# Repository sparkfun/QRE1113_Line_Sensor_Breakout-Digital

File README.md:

SparkFun Line Sensor Breakout - QRE1113 (Digital)
========================================

[*SparkFun Line Sensor Breakout - QRE1113 (Digital) (ROB-09454)*](https://www.sparkfun.com/products/9454)

This version of the QRE1113 breakout board features a digital output, using a capacitor discharge circuit to measure the amount of reflection. 
This tiny board is perfect for line sensing when only digital I/O is available, and can be used in both 3.3V and 5V systems.

Repository Contents
-------------------

* **/Hardware** - Eagle design files (.brd, .sch)
* **/Production** - Production panel files (.brd)

Documentation
--------------
* **[SparkFun Fritzing repo](https://github.com/sparkfun/Fritzing_Parts)** - Fritzing diagrams for SparkFun products.
* **[SparkFun 3D Model repo](https://github.com/sparkfun/3D_Models)** - 3D models of SparkFun products. 

Product Versions
----------------
* [ROB-09454](https://www.sparkfun.com/products/9454)- Digital version of the breakout board. 
* [ROB-09453] (https://www.sparkfun.com/products/9453)- Analog version of the breakout board. 

License Information
-------------------
This product is _**open source**_! 

The **hardware** is released under [Creative Commons ShareAlike 4.0 International](https://creativecommons.org/licenses/by-sa/4.0/).

Please use, reuse, and modify these files as you see fit. Please maintain attribution to SparkFun Electronics and release anything derivative under the same license.

Distributed as-is; no warranty is given.

- Your friends at SparkFun.

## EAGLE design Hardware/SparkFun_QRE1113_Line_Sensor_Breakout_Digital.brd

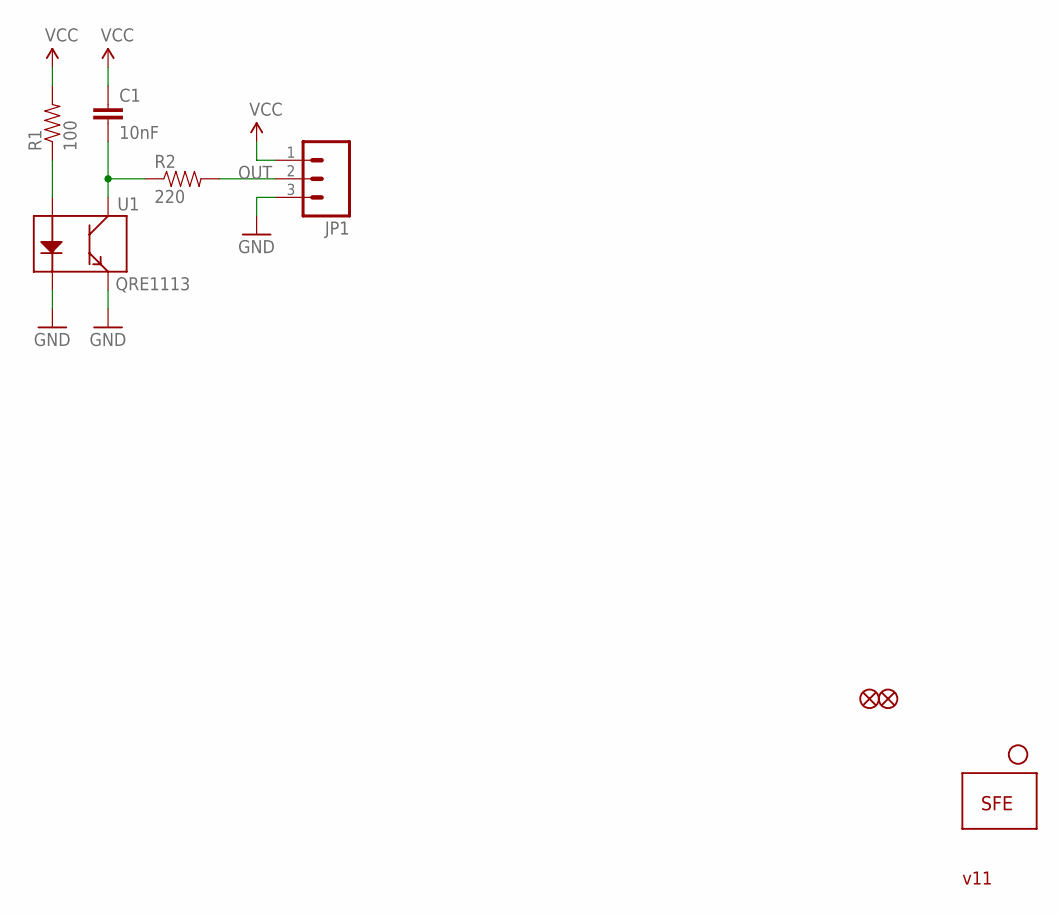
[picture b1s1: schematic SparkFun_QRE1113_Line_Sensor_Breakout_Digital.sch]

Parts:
C1: 10nF; 0402-CAP
FID1, FID2: FIDUCIALUFIDUCIAL; MICRO-FIDUCIAL
JP1: M03PTH; 1X03
JP2: LOGO-SFESK; SFE-LOGO-FLAME
JP3: STAND-OFF
R1: 100; 0402-RES
R2: 220; 0402-RES
U1: QRE1113

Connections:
GND: JP1.3, U1.2 (K), U1.4 (E)
unnamed: R1.1, U1.1 (A)
OUT: JP1.2, R2.2
OUT1: C1.2, R2.1, U1.3 (C)
VCC: C1.1, JP1.1, R1.2

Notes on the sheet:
v11

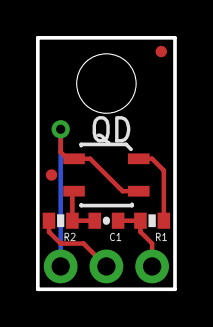
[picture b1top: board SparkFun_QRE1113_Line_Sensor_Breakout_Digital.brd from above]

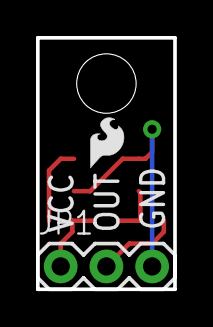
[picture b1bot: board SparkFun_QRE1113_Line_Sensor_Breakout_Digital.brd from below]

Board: 2 copper layers, 7.6 x 14.0 mm, 9 parts (2 on the bottom side), 5 nets.

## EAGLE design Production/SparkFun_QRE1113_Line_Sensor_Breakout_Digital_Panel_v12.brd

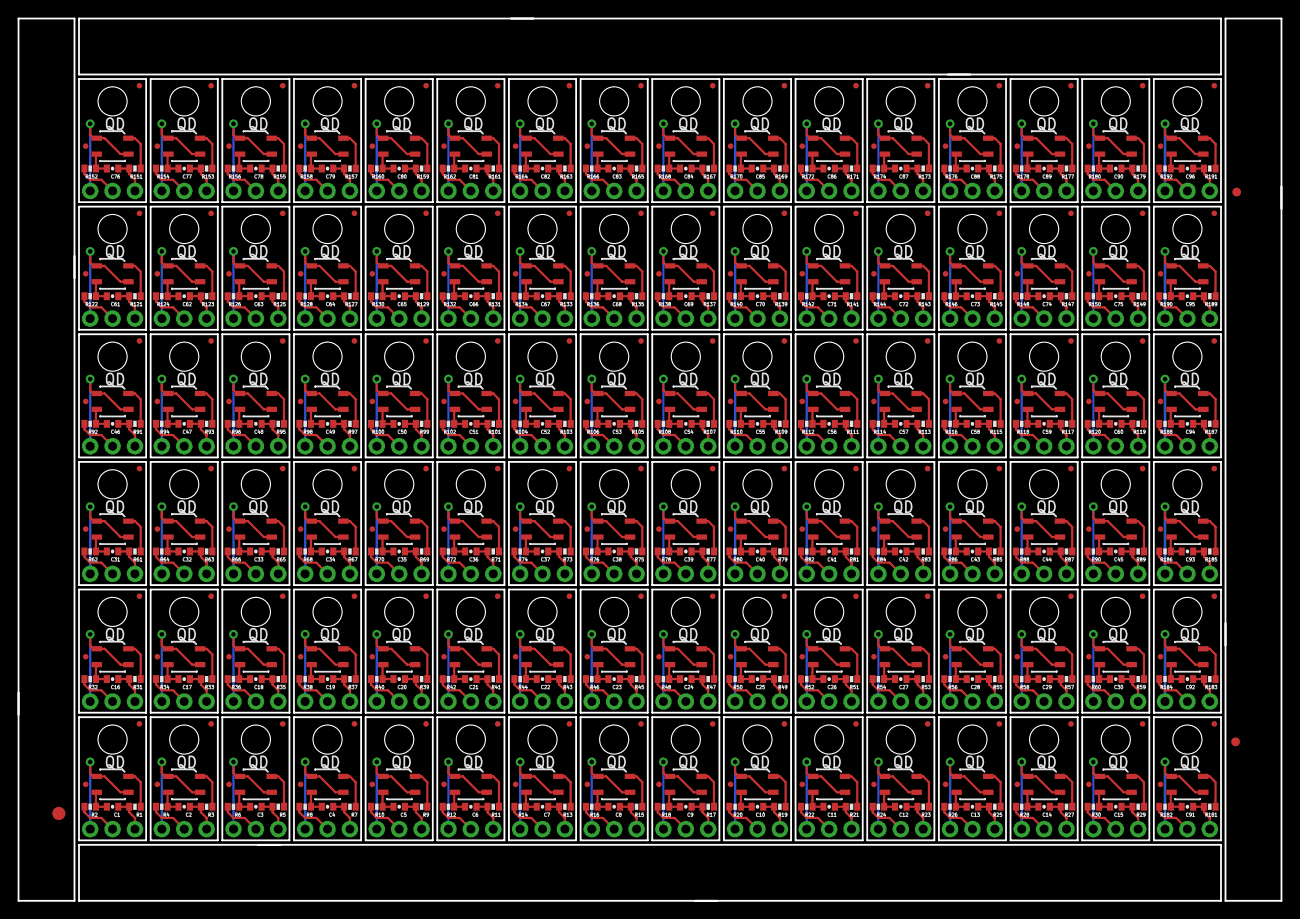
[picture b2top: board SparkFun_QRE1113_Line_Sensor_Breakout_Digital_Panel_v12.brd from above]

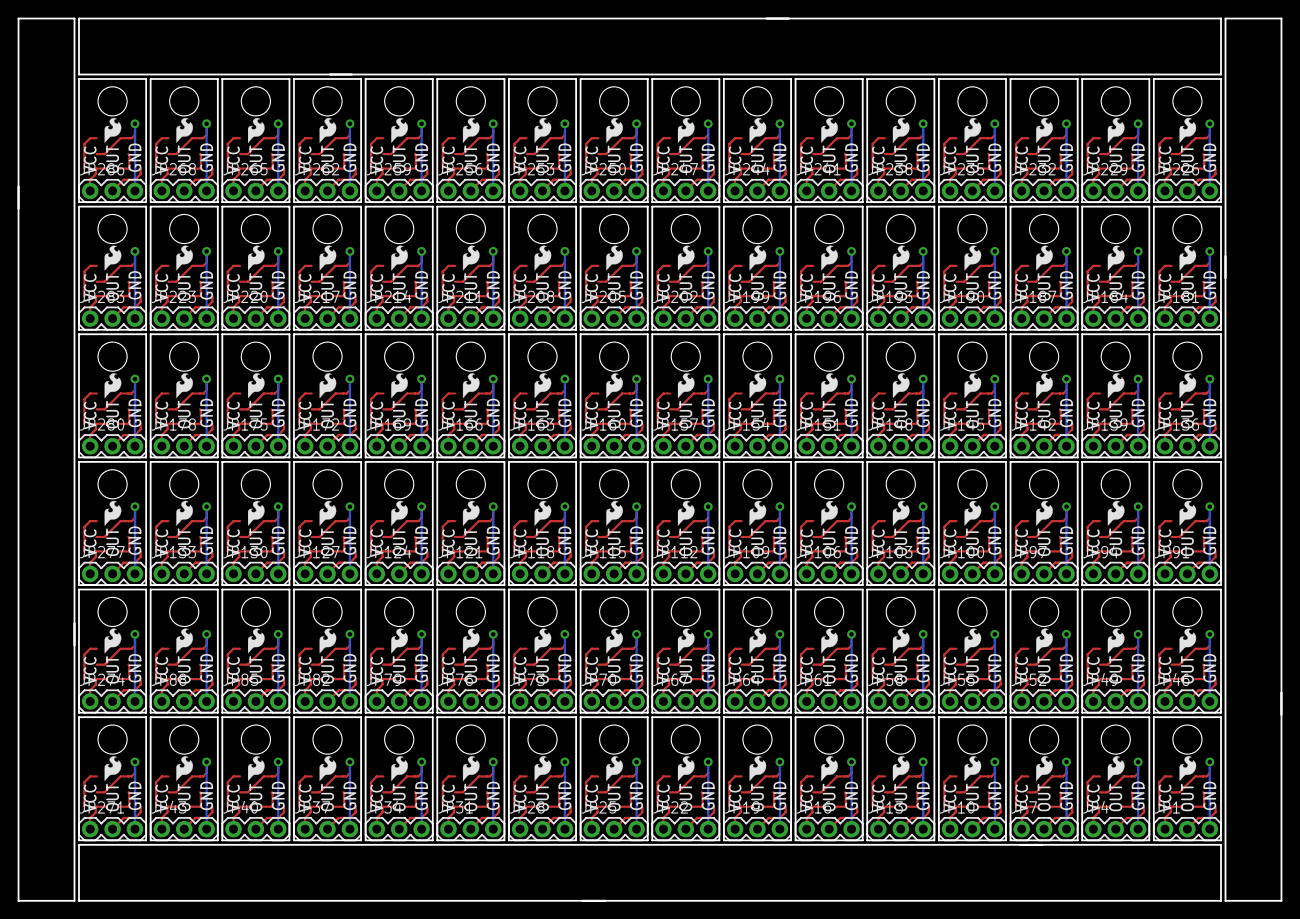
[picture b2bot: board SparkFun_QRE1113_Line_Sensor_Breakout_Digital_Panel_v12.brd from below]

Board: 2 copper layers, 143.3 x 100.1 mm, 867 parts (192 on the bottom side), 480 nets.

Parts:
C1, C2, C3, C4, C5, C6, C7, C8, C9, C10, C11, C12, C13, C14, C15, C16, C17, C18, C19, C20, C21, C22, C23, C24, C25, C26, C27, C28, C29, C30, C31, C32, C33, C34, C35, C36, C37, C38, C39, C40, C41, C42, C43, C44, C45, C46, C47, C48, C49, C50, C51, C52, C53, C54, C55, C56, C57, C58, C59, C60, C61, C62, C63, C64, C65, C66, C67, C68, C69, C70, C71, C72, C73, C74, C75, C76, C77, C78, C79, C80, C81, C82, C83, C84, C85, C86, C87, C88, C89, C90, C91, C92, C93, C94, C95, C96: 10nF; 0402-CAP
E$1: FIDUCIAL-1.5X3
E$5, E$7: FIDUCIAL-1X2
FID1, FID2, FID3, FID4, FID5, FID6, FID7, FID8, FID9, FID10, FID11, FID12, FID13, FID14, FID15, FID16, FID17, FID18, FID19, FID20, FID21, FID22, FID23, FID24, FID25, FID26, FID27, FID28, FID29, FID30, FID31, FID32, FID33, FID34, FID35, FID36, FID37, FID38, FID39, FID40, FID41, FID42, FID43, FID44, FID45, FID46, FID47, FID48, FID49, FID50, FID51, FID52, FID53, FID54, FID55, FID56, FID57, FID58, FID59, FID60, FID61, FID62, FID63, FID64, FID65, FID66, FID67, FID68, FID69, FID70, FID71, FID72, FID73, FID74, FID75, FID76, FID77, FID78, FID79, FID80, FID81, FID82, FID83, FID84, FID85, FID86, FID87, FID88, FID89, FID90, FID91, FID92, FID93, FID94, FID95, FID96, FID97, FID98, FID99, FID100, FID101, FID102, FID103, FID104, FID105, FID106, FID107, FID108, FID109, FID110, FID111, FID112, FID113, FID114, FID115, FID116, FID117, FID118, FID119, FID120, FID121, FID122, FID123, FID124, FID125, FID126, FID127, FID128, FID129, FID130, FID131, FID132, FID133, FID134, FID135, FID136, FID137, FID138, FID139, FID140, FID141, FID142, FID143, FID144, FID145, FID146, FID147, FID148, FID149, FID150, FID151, FID152, FID153, FID154, FID155, FID156, FID157, FID158, FID159, FID160, FID161, FID162, FID163, FID164, FID165, FID166, FID167, FID168, FID169, FID170, FID171, FID172, FID173, FID174, FID175, FID176, FID177, FID178, FID179, FID180, FID181, FID182, FID183, FID184, FID185, FID186, FID187, FID188, FID189, FID190, FID191, FID192: FIDUCIALUFIDUCIAL; MICRO-FIDUCIAL
JP1, JP4, JP7, JP10, JP13, JP16, JP19, JP22, JP25, JP28, JP31, JP34, JP37, JP40, JP43, JP46, JP49, JP52, JP55, JP58, JP61, JP64, JP67, JP70, JP73, JP76, JP79, JP82, JP85, JP88, JP91, JP94, JP97, JP100, JP103, JP106, JP109, JP112, JP115, JP118, JP121, JP124, JP127, JP130, JP133, JP136, JP139, JP142, JP145, JP148, JP151, JP154, JP157, JP160, JP163, JP166, JP169, JP172, JP175, JP178, JP181, JP184, JP187, JP190, JP193, JP196, JP199, JP202, JP205, JP208, JP211, JP214, JP217, JP220, JP223, JP226, JP229, JP232, JP235, JP238, JP241, JP244, JP247, JP250, JP253, JP256, JP259, JP262, JP265, JP268, JP271, JP274, JP277, JP280, JP283, JP286: 1X03
JP2, JP5, JP8, JP11, JP14, JP17, JP20, JP23, JP26, JP29, JP32, JP35, JP38, JP41, JP44, JP47, JP50, JP53, JP56, JP59, JP62, JP65, JP68, JP71, JP74, JP77, JP80, JP83, JP86, JP89, JP92, JP95, JP98, JP101, JP104, JP107, JP110, JP113, JP116, JP119, JP122, JP125, JP128, JP131, JP134, JP137, JP140, JP143, JP146, JP149, JP152, JP155, JP158, JP161, JP164, JP167, JP170, JP173, JP176, JP179, JP182, JP185, JP188, JP191, JP194, JP197, JP200, JP203, JP206, JP209, JP212, JP215, JP218, JP221, JP224, JP227, JP230, JP233, JP236, JP239, JP242, JP245, JP248, JP251, JP254, JP257, JP260, JP263, JP266, JP269, JP272, JP275, JP278, JP281, JP284, JP287: LOGO-SFESK; SFE-LOGO-FLAME
JP3, JP6, JP9, JP12, JP15, JP18, JP21, JP24, JP27, JP30, JP33, JP36, JP39, JP42, JP45, JP48, JP51, JP54, JP57, JP60, JP63, JP66, JP69, JP72, JP75, JP78, JP81, JP84, JP87, JP90, JP93, JP96, JP99, JP102, JP105, JP108, JP111, JP114, JP117, JP120, JP123, JP126, JP129, JP132, JP135, JP138, JP141, JP144, JP147, JP150, JP153, JP156, JP159, JP162, JP165, JP168, JP171, JP174, JP177, JP180, JP183, JP186, JP189, JP192, JP195, JP198, JP201, JP204, JP207, JP210, JP213, JP216, JP219, JP222, JP225, JP228, JP231, JP234, JP237, JP240, JP243, JP246, JP249, JP252, JP255, JP258, JP261, JP264, JP267, JP270, JP273, JP276, JP279, JP282, JP285, JP288: STAND-OFF
R1, R3, R5, R7, R9, R11, R13, R15, R17, R19, R21, R23, R25, R27, R29, R31, R33, R35, R37, R39, R41, R43, R45, R47, R49, R51, R53, R55, R57, R59, R61, R63, R65, R67, R69, R71, R73, R75, R77, R79, R81, R83, R85, R87, R89, R91, R93, R95, R97, R99, R101, R103, R105, R107, R109, R111, R113, R115, R117, R119, R121, R123, R125, R127, R129, R131, R133, R135, R137, R139, R141, R143, R145, R147, R149, R151, R153, R155, R157, R159, R161, R163, R165, R167, R169, R171, R173, R175, R177, R179, R181, R183, R185, R187, R189, R191: 100; 0402-RES
R2, R4, R6, R8, R10, R12, R14, R16, R18, R20, R22, R24, R26, R28, R30, R32, R34, R36, R38, R40, R42, R44, R46, R48, R50, R52, R54, R56, R58, R60, R62, R64, R66, R68, R70, R72, R74, R76, R78, R80, R82, R84, R86, R88, R90, R92, R94, R96, R98, R100, R102, R104, R106, R108, R110, R112, R114, R116, R118, R120, R122, R124, R126, R128, R130, R132, R134, R136, R138, R140, R142, R144, R146, R148, R150, R152, R154, R156, R158, R160, R162, R164, R166, R168, R170, R172, R174, R176, R178, R180, R182, R184, R186, R188, R190, R192: 220; 0402-RES
U1, U2, U3, U4, U5, U6, U7, U8, U9, U10, U11, U12, U13, U14, U15, U16, U17, U18, U19, U20, U21, U22, U23, U24, U25, U26, U27, U28, U29, U30, U31, U32, U33, U34, U35, U36, U37, U38, U39, U40, U41, U42, U43, U44, U45, U46, U47, U48, U49, U50, U51, U52, U53, U54, U55, U56, U57, U58, U59, U60, U61, U62, U63, U64, U65, U66, U67, U68, U69, U70, U71, U72, U73, U74, U75, U76, U77, U78, U79, U80, U81, U82, U83, U84, U85, U86, U87, U88, U89, U90, U91, U92, U93, U94, U95, U96: QRE1113

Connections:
GND: JP1.3, U1.2, U1.4
GND1: JP4.3, U2.2, U2.4
GND2: JP7.3, U3.2, U3.4
GND3: JP10.3, U4.2, U4.4
GND4: JP13.3, U5.2, U5.4
GND5: JP16.3, U6.2, U6.4
GND6: JP19.3, U7.2, U7.4
GND7: JP22.3, U8.2, U8.4
GND8: JP25.3, U9.2, U9.4
GND9: JP28.3, U10.2, U10.4
GND10: JP31.3, U11.2, U11.4
GND11: JP34.3, U12.2, U12.4
GND12: JP37.3, U13.2, U13.4
GND13: JP40.3, U14.2, U14.4
GND14: JP43.3, U15.2, U15.4
GND15: JP46.3, U16.2, U16.4
GND16: JP49.3, U17.2, U17.4
GND17: JP52.3, U18.2, U18.4
GND18: JP55.3, U19.2, U19.4
GND19: JP58.3, U20.2, U20.4
GND20: JP61.3, U21.2, U21.4
GND21: JP64.3, U22.2, U22.4
GND22: JP67.3, U23.2, U23.4
GND23: JP70.3, U24.2, U24.4
GND24: JP73.3, U25.2, U25.4
GND25: JP76.3, U26.2, U26.4
GND26: JP79.3, U27.2, U27.4
GND27: JP82.3, U28.2, U28.4
GND28: JP85.3, U29.2, U29.4
GND29: JP88.3, U30.2, U30.4
GND30: JP91.3, U31.2, U31.4
GND31: JP94.3, U32.2, U32.4
GND32: JP97.3, U33.2, U33.4
GND33: JP100.3, U34.2, U34.4
GND34: JP103.3, U35.2, U35.4
GND35: JP106.3, U36.2, U36.4
GND36: JP109.3, U37.2, U37.4
GND37: JP112.3, U38.2, U38.4
GND38: JP115.3, U39.2, U39.4
GND39: JP118.3, U40.2, U40.4
GND40: JP121.3, U41.2, U41.4
GND41: JP124.3, U42.2, U42.4
GND42: JP127.3, U43.2, U43.4
GND43: JP130.3, U44.2, U44.4
GND44: JP133.3, U45.2, U45.4
GND45: JP136.3, U46.2, U46.4
GND46: JP139.3, U47.2, U47.4
GND47: JP142.3, U48.2, U48.4
GND48: JP145.3, U49.2, U49.4
GND49: JP148.3, U50.2, U50.4
GND50: JP151.3, U51.2, U51.4
GND51: JP154.3, U52.2, U52.4
GND52: JP157.3, U53.2, U53.4
GND53: JP160.3, U54.2, U54.4
GND54: JP163.3, U55.2, U55.4
GND55: JP166.3, U56.2, U56.4
GND56: JP169.3, U57.2, U57.4
GND57: JP172.3, U58.2, U58.4
GND58: JP175.3, U59.2, U59.4
GND59: JP178.3, U60.2, U60.4
GND60: JP181.3, U61.2, U61.4
GND61: JP184.3, U62.2, U62.4
GND62: JP187.3, U63.2, U63.4
GND63: JP190.3, U64.2, U64.4
GND64: JP193.3, U65.2, U65.4
GND65: JP196.3, U66.2, U66.4
GND66: JP199.3, U67.2, U67.4
GND67: JP202.3, U68.2, U68.4
GND68: JP205.3, U69.2, U69.4
GND69: JP208.3, U70.2, U70.4
GND70: JP211.3, U71.2, U71.4
GND71: JP214.3, U72.2, U72.4
GND72: JP217.3, U73.2, U73.4
GND73: JP220.3, U74.2, U74.4
GND74: JP223.3, U75.2, U75.4
GND75: JP226.3, U76.2, U76.4
GND76: JP229.3, U77.2, U77.4
GND77: JP232.3, U78.2, U78.4
GND78: JP235.3, U79.2, U79.4
GND79: JP238.3, U80.2, U80.4
GND80: JP241.3, U81.2, U81.4
GND81: JP244.3, U82.2, U82.4
GND82: JP247.3, U83.2, U83.4
GND83: JP250.3, U84.2, U84.4
GND84: JP253.3, U85.2, U85.4
GND85: JP256.3, U86.2, U86.4
GND86: JP259.3, U87.2, U87.4
GND87: JP262.3, U88.2, U88.4
GND88: JP265.3, U89.2, U89.4
GND89: JP268.3, U90.2, U90.4
GND90: JP271.3, U91.2, U91.4
GND91: JP274.3, U92.2, U92.4
GND92: JP277.3, U93.2, U93.4
GND93: JP280.3, U94.2, U94.4
GND94: JP283.3, U95.2, U95.4
GND95: JP286.3, U96.2, U96.4
unnamed: R1.1, U1.1
unnamed: R3.1, U2.1
unnamed: R5.1, U3.1
unnamed: R7.1, U4.1
unnamed: R9.1, U5.1
unnamed: R11.1, U6.1
unnamed: R13.1, U7.1
unnamed: R15.1, U8.1
unnamed: R17.1, U9.1
unnamed: R19.1, U10.1
unnamed: R21.1, U11.1
unnamed: R23.1, U12.1
unnamed: R25.1, U13.1
unnamed: R27.1, U14.1
unnamed: R29.1, U15.1
unnamed: R31.1, U16.1
unnamed: R33.1, U17.1
unnamed: R35.1, U18.1
unnamed: R37.1, U19.1
unnamed: R39.1, U20.1
unnamed: R41.1, U21.1
unnamed: R43.1, U22.1
unnamed: R45.1, U23.1
unnamed: R47.1, U24.1
unnamed: R49.1, U25.1
unnamed: R51.1, U26.1
unnamed: R53.1, U27.1
unnamed: R55.1, U28.1
unnamed: R57.1, U29.1
unnamed: R59.1, U30.1
unnamed: R61.1, U31.1
unnamed: R63.1, U32.1
unnamed: R65.1, U33.1
unnamed: R67.1, U34.1
unnamed: R69.1, U35.1
unnamed: R71.1, U36.1
unnamed: R73.1, U37.1
unnamed: R75.1, U38.1
unnamed: R77.1, U39.1
unnamed: R79.1, U40.1
unnamed: R81.1, U41.1
unnamed: R83.1, U42.1
unnamed: R85.1, U43.1
unnamed: R87.1, U44.1
unnamed: R89.1, U45.1
unnamed: R91.1, U46.1
unnamed: R93.1, U47.1
unnamed: R95.1, U48.1
unnamed: R97.1, U49.1
unnamed: R99.1, U50.1
unnamed: R101.1, U51.1
unnamed: R103.1, U52.1
unnamed: R105.1, U53.1
unnamed: R107.1, U54.1
unnamed: R109.1, U55.1
unnamed: R111.1, U56.1
unnamed: R113.1, U57.1
unnamed: R115.1, U58.1
unnamed: R117.1, U59.1
unnamed: R119.1, U60.1
unnamed: R121.1, U61.1
unnamed: R123.1, U62.1
unnamed: R125.1, U63.1
unnamed: R127.1, U64.1
unnamed: R129.1, U65.1
unnamed: R131.1, U66.1
unnamed: R133.1, U67.1
unnamed: R135.1, U68.1
unnamed: R137.1, U69.1
unnamed: R139.1, U70.1
unnamed: R141.1, U71.1
unnamed: R143.1, U72.1
unnamed: R145.1, U73.1
unnamed: R147.1, U74.1
unnamed: R149.1, U75.1
unnamed: R151.1, U76.1
unnamed: R153.1, U77.1
unnamed: R155.1, U78.1
unnamed: R157.1, U79.1
unnamed: R159.1, U80.1
unnamed: R161.1, U81.1
unnamed: R163.1, U82.1
unnamed: R165.1, U83.1
unnamed: R167.1, U84.1
unnamed: R169.1, U85.1
unnamed: R171.1, U86.1
unnamed: R173.1, U87.1
unnamed: R175.1, U88.1
unnamed: R177.1, U89.1
unnamed: R179.1, U90.1
unnamed: R181.1, U91.1
unnamed: R183.1, U92.1
unnamed: R185.1, U93.1
unnamed: R187.1, U94.1
unnamed: R189.1, U95.1
unnamed: R191.1, U96.1
OUT: JP1.2, R2.2
OUT1: C1.2, R2.1, U1.3
OUT2: C2.2, R4.1, U2.3
OUT3: JP4.2, R4.2
OUT4: C3.2, R6.1, U3.3
OUT5: JP7.2, R6.2
OUT6: C4.2, R8.1, U4.3
OUT7: JP10.2, R8.2
OUT8: C5.2, R10.1, U5.3
OUT9: JP13.2, R10.2
OUT10: C6.2, R12.1, U6.3
OUT11: JP16.2, R12.2
OUT12: C7.2, R14.1, U7.3
OUT13: JP19.2, R14.2
OUT14: C8.2, R16.1, U8.3
OUT15: JP22.2, R16.2
OUT16: C9.2, R18.1, U9.3
OUT17: JP25.2, R18.2
OUT18: C10.2, R20.1, U10.3
OUT19: JP28.2, R20.2
OUT20: C11.2, R22.1, U11.3
OUT21: JP31.2, R22.2
OUT22: C12.2, R24.1, U12.3
OUT23: JP34.2, R24.2
OUT24: C13.2, R26.1, U13.3
OUT25: JP37.2, R26.2
OUT26: C14.2, R28.1, U14.3
OUT27: JP40.2, R28.2
OUT28: C15.2, R30.1, U15.3
OUT29: JP43.2, R30.2
OUT30: C16.2, R32.1, U16.3
OUT31: JP46.2, R32.2
OUT32: C17.2, R34.1, U17.3
OUT33: JP49.2, R34.2
OUT34: C18.2, R36.1, U18.3
OUT35: JP52.2, R36.2
OUT36: C19.2, R38.1, U19.3
OUT37: JP55.2, R38.2
OUT38: C20.2, R40.1, U20.3
OUT39: JP58.2, R40.2
OUT40: C21.2, R42.1, U21.3
OUT41: JP61.2, R42.2
OUT42: C22.2, R44.1, U22.3
OUT43: JP64.2, R44.2
OUT44: C23.2, R46.1, U23.3
OUT45: JP67.2, R46.2
OUT46: C24.2, R48.1, U24.3
OUT47: JP70.2, R48.2
OUT48: C25.2, R50.1, U25.3
OUT49: JP73.2, R50.2
OUT50: C26.2, R52.1, U26.3
OUT51: JP76.2, R52.2
OUT52: C27.2, R54.1, U27.3
OUT53: JP79.2, R54.2
OUT54: C28.2, R56.1, U28.3
OUT55: JP82.2, R56.2
OUT56: C29.2, R58.1, U29.3
OUT57: JP85.2, R58.2
OUT58: C30.2, R60.1, U30.3
OUT59: JP88.2, R60.2
OUT60: C31.2, R62.1, U31.3
OUT61: JP91.2, R62.2
OUT62: C32.2, R64.1, U32.3
OUT63: JP94.2, R64.2
OUT64: C33.2, R66.1, U33.3
OUT65: JP97.2, R66.2
OUT66: C34.2, R68.1, U34.3
OUT67: JP100.2, R68.2
OUT68: C35.2, R70.1, U35.3
OUT69: JP103.2, R70.2
OUT70: C36.2, R72.1, U36.3
OUT71: JP106.2, R72.2
OUT72: C37.2, R74.1, U37.3
OUT73: JP109.2, R74.2
OUT74: C38.2, R76.1, U38.3
OUT75: JP112.2, R76.2
OUT76: C39.2, R78.1, U39.3
OUT77: JP115.2, R78.2
OUT78: C40.2, R80.1, U40.3
OUT79: JP118.2, R80.2
OUT80: C41.2, R82.1, U41.3
OUT81: JP121.2, R82.2
OUT82: C42.2, R84.1, U42.3
OUT83: JP124.2, R84.2
OUT84: C43.2, R86.1, U43.3
OUT85: JP127.2, R86.2
OUT86: C44.2, R88.1, U44.3
OUT87: JP130.2, R88.2
OUT88: C45.2, R90.1, U45.3
OUT89: JP133.2, R90.2
OUT90: C46.2, R92.1, U46.3
OUT91: JP136.2, R92.2
OUT92: C47.2, R94.1, U47.3
OUT93: JP139.2, R94.2
OUT94: C48.2, R96.1, U48.3
OUT95: JP142.2, R96.2
OUT96: C49.2, R98.1, U49.3
OUT97: JP145.2, R98.2
OUT98: C50.2, R100.1, U50.3
OUT99: JP148.2, R100.2
OUT100: C51.2, R102.1, U51.3
OUT101: JP151.2, R102.2
OUT102: C52.2, R104.1, U52.3
OUT103: JP154.2, R104.2
OUT104: C53.2, R106.1, U53.3
OUT105: JP157.2, R106.2
OUT106: C54.2, R108.1, U54.3
OUT107: JP160.2, R108.2
OUT108: C55.2, R110.1, U55.3
OUT109: JP163.2, R110.2
OUT110: C56.2, R112.1, U56.3
OUT111: JP166.2, R112.2
OUT112: C57.2, R114.1, U57.3
OUT113: JP169.2, R114.2
OUT114: C58.2, R116.1, U58.3
OUT115: JP172.2, R116.2
OUT116: C59.2, R118.1, U59.3
OUT117: JP175.2, R118.2
OUT118: C60.2, R120.1, U60.3
OUT119: JP178.2, R120.2
OUT120: C61.2, R122.1, U61.3
OUT121: JP181.2, R122.2
OUT122: C62.2, R124.1, U62.3
OUT123: JP184.2, R124.2
OUT124: C63.2, R126.1, U63.3
OUT125: JP187.2, R126.2
OUT126: C64.2, R128.1, U64.3
OUT127: JP190.2, R128.2
OUT128: C65.2, R130.1, U65.3
OUT129: JP193.2, R130.2
OUT130: C66.2, R132.1, U66.3
OUT131: JP196.2, R132.2
OUT132: C67.2, R134.1, U67.3
OUT133: JP199.2, R134.2
OUT134: C68.2, R136.1, U68.3
OUT135: JP202.2, R136.2
OUT136: C69.2, R138.1, U69.3
OUT137: JP205.2, R138.2
OUT138: C70.2, R140.1, U70.3
OUT139: JP208.2, R140.2
OUT140: C71.2, R142.1, U71.3
OUT141: JP211.2, R142.2
OUT142: C72.2, R144.1, U72.3
OUT143: JP214.2, R144.2
OUT144: C73.2, R146.1, U73.3
OUT145: JP217.2, R146.2
OUT146: C74.2, R148.1, U74.3
OUT147: JP220.2, R148.2
OUT148: C75.2, R150.1, U75.3
OUT149: JP223.2, R150.2
OUT150: C76.2, R152.1, U76.3
OUT151: JP226.2, R152.2
OUT152: C77.2, R154.1, U77.3
OUT153: JP229.2, R154.2
OUT154: C78.2, R156.1, U78.3
OUT155: JP232.2, R156.2
OUT156: C79.2, R158.1, U79.3
OUT157: JP235.2, R158.2
OUT158: C80.2, R160.1, U80.3
OUT159: JP238.2, R160.2
OUT160: C81.2, R162.1, U81.3
OUT161: JP241.2, R162.2
OUT162: C82.2, R164.1, U82.3
OUT163: JP244.2, R164.2
OUT164: C83.2, R166.1, U83.3
OUT165: JP247.2, R166.2
OUT166: C84.2, R168.1, U84.3
OUT167: JP250.2, R168.2
OUT168: C85.2, R170.1, U85.3
OUT169: JP253.2, R170.2
OUT170: C86.2, R172.1, U86.3
OUT171: JP256.2, R172.2
OUT172: C87.2, R174.1, U87.3
OUT173: JP259.2, R174.2
OUT174: C88.2, R176.1, U88.3
OUT175: JP262.2, R176.2
OUT176: C89.2, R178.1, U89.3
OUT177: JP265.2, R178.2
OUT178: C90.2, R180.1, U90.3
OUT179: JP268.2, R180.2
OUT180: C91.2, R182.1, U91.3
OUT181: JP271.2, R182.2
OUT182: C92.2, R184.1, U92.3
OUT183: JP274.2, R184.2
OUT184: C93.2, R186.1, U93.3
OUT185: JP277.2, R186.2
OUT186: C94.2, R188.1, U94.3
OUT187: JP280.2, R188.2
OUT188: C95.2, R190.1, U95.3
OUT189: JP283.2, R190.2
OUT190: C96.2, R192.1, U96.3
OUT191: JP286.2, R192.2
VCC: C1.1, JP1.1, R1.2
VCC1: C2.1, JP4.1, R3.2
VCC2: C3.1, JP7.1, R5.2
VCC3: C4.1, JP10.1, R7.2
VCC4: C5.1, JP13.1, R9.2
VCC5: C6.1, JP16.1, R11.2
VCC6: C7.1, JP19.1, R13.2
VCC7: C8.1, JP22.1, R15.2
VCC8: C9.1, JP25.1, R17.2
VCC9: C10.1, JP28.1, R19.2
VCC10: C11.1, JP31.1, R21.2
VCC11: C12.1, JP34.1, R23.2
VCC12: C13.1, JP37.1, R25.2
VCC13: C14.1, JP40.1, R27.2
VCC14: C15.1, JP43.1, R29.2
VCC15: C16.1, JP46.1, R31.2
VCC16: C17.1, JP49.1, R33.2
VCC17: C18.1, JP52.1, R35.2
VCC18: C19.1, JP55.1, R37.2
VCC19: C20.1, JP58.1, R39.2
VCC20: C21.1, JP61.1, R41.2
VCC21: C22.1, JP64.1, R43.2
VCC22: C23.1, JP67.1, R45.2
VCC23: C24.1, JP70.1, R47.2
VCC24: C25.1, JP73.1, R49.2
VCC25: C26.1, JP76.1, R51.2
VCC26: C27.1, JP79.1, R53.2
VCC27: C28.1, JP82.1, R55.2
VCC28: C29.1, JP85.1, R57.2
VCC29: C30.1, JP88.1, R59.2
VCC30: C31.1, JP91.1, R61.2
VCC31: C32.1, JP94.1, R63.2
VCC32: C33.1, JP97.1, R65.2
VCC33: C34.1, JP100.1, R67.2
VCC34: C35.1, JP103.1, R69.2
VCC35: C36.1, JP106.1, R71.2
VCC36: C37.1, JP109.1, R73.2
VCC37: C38.1, JP112.1, R75.2
VCC38: C39.1, JP115.1, R77.2
VCC39: C40.1, JP118.1, R79.2
VCC40: C41.1, JP121.1, R81.2
VCC41: C42.1, JP124.1, R83.2
VCC42: C43.1, JP127.1, R85.2
VCC43: C44.1, JP130.1, R87.2
VCC44: C45.1, JP133.1, R89.2
VCC45: C46.1, JP136.1, R91.2
VCC46: C47.1, JP139.1, R93.2
VCC47: C48.1, JP142.1, R95.2
VCC48: C49.1, JP145.1, R97.2
VCC49: C50.1, JP148.1, R99.2
VCC50: C51.1, JP151.1, R101.2
VCC51: C52.1, JP154.1, R103.2
VCC52: C53.1, JP157.1, R105.2
VCC53: C54.1, JP160.1, R107.2
VCC54: C55.1, JP163.1, R109.2
VCC55: C56.1, JP166.1, R111.2
VCC56: C57.1, JP169.1, R113.2
VCC57: C58.1, JP172.1, R115.2
VCC58: C59.1, JP175.1, R117.2
VCC59: C60.1, JP178.1, R119.2
VCC60: C61.1, JP181.1, R121.2
VCC61: C62.1, JP184.1, R123.2
VCC62: C63.1, JP187.1, R125.2
VCC63: C64.1, JP190.1, R127.2
VCC64: C65.1, JP193.1, R129.2
VCC65: C66.1, JP196.1, R131.2
VCC66: C67.1, JP199.1, R133.2
VCC67: C68.1, JP202.1, R135.2
VCC68: C69.1, JP205.1, R137.2
VCC69: C70.1, JP208.1, R139.2
VCC70: C71.1, JP211.1, R141.2
VCC71: C72.1, JP214.1, R143.2
VCC72: C73.1, JP217.1, R145.2
VCC73: C74.1, JP220.1, R147.2
VCC74: C75.1, JP223.1, R149.2
VCC75: C76.1, JP226.1, R151.2
VCC76: C77.1, JP229.1, R153.2
VCC77: C78.1, JP232.1, R155.2
VCC78: C79.1, JP235.1, R157.2
VCC79: C80.1, JP238.1, R159.2
VCC80: C81.1, JP241.1, R161.2
VCC81: C82.1, JP244.1, R163.2
VCC82: C83.1, JP247.1, R165.2
VCC83: C84.1, JP250.1, R167.2
VCC84: C85.1, JP253.1, R169.2
VCC85: C86.1, JP256.1, R171.2
VCC86: C87.1, JP259.1, R173.2
VCC87: C88.1, JP262.1, R175.2
VCC88: C89.1, JP265.1, R177.2
VCC89: C90.1, JP268.1, R179.2
VCC90: C91.1, JP271.1, R181.2
VCC91: C92.1, JP274.1, R183.2
VCC92: C93.1, JP277.1, R185.2
VCC93: C94.1, JP280.1, R187.2
VCC94: C95.1, JP283.1, R189.2
VCC95: C96.1, JP286.1, R191.2

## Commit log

2015-05-04 Adding hardware files, updating README
2015-12-11 added board fiducials
2015-12-14 created panel v12
2015-12-16 made panel bigger

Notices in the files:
parts and their libraries:
SparkFun-Aesthetics: Licensing: Creative Commons ShareAlike 4.0 International - https://creativecommons.org/licenses/by-sa/4.0
